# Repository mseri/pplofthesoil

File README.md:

# People of the Soil
**(co-winners of the London Nasa Space Apps Challenge 2013)** 

During the Space Apps Challenge 2013, at the Google Campus in London, we have developed **Project Soil**: an extremely cheap and easy to use system to collect and manage soil data.

We kept in mind that not all the world is as lucky as us and there are plenty of places where internet is slow or completely absent and where there is much less money around. 

**Project Soil** is an open system that includes:

- an extremely cheap (~3£) digital soil testing kit to collect data, and eventually send it
- a light protocol to send the data using web, apps or even SMS and collect it on a centralised database
- an API to disseminate information via SMS or web
- a wonderful and light web application that can run on old and recent phones and gives access to the data with a simple and nice interface.

# Project Soil

We spent the first part of the challeng looking at all our different backgrounds and skills and reformulating the challenge in a series of smaller ones that we feelt we could face. 

As you can see from the image below, **Project Soil** is made by three big interlaced projects, each of them with a particular focus: acquiring data, collecting it and make it available.

## The probe

In this part of the projected we aimed to create a proof-of-concept soil testing kit that could be miniaturised and mass produced. This can then upload recorded soil data, taken over a period of several weeks, to a central database via a phone application or computer interface.

The hardware team realized in an amazingly short time a working prototype of probe to collect soil data. In the first version an Arduino was collecting data from various sensors and sending it to a Rasperry Pi programmed to forward it to our database.

In addition, the aim was to create a PCB schematic and layout to implement this system realistically and cost such a device. CAD models were created to aid development and concept presentation.

The project uses a DS18B20 temperature sensor and a transistor amplified simple moisture sensor.

Moisture is displayed as an estimated percentage volume of water to soil. Completely soaked soil will hold up to around 50% water content and so a measurement of resistance of pure water is taken as the calibration mark for 50% and the probe held in air is taken as the calibration for 0%.

The hardware prototype is a proof of concept, a final device should use a much cheaper MPU such as an ATMEGA48A-MU 4K memory, 8-Bit MPU. This can be sourced (in bulk) for less than 80p per unit.

### The probe and its price breakdown

In fact, from that prototype the hardware team engineered a small and cheap device that you can simply plug in the field and leave alone collecting the data. Afterward it is enough to have a USB connection to collect the data and send it to our servers.

For whom may be interested, the price of the final device can be overestimated as follows:

- ATMEGA48A £0.80   
- Resistor £0.10   
- DS18B20 £0.85   
- CR2032 Coin Cell £0.39   
- Coin cell holder £0.20   
- PCB manufacture £1.00   

**Total £3.34**

## The SMS service

Keeping in mind that not all the world is covered by internet, we used the twilio API to create a service to send the data directly through SMS. This makes it good for use in more developing regions of the world.

Send a text to _01952 787011_ containing a list of readings for the following parameters pH, temperature, moisture, lat/latitude and long/longitude and then will be added to the dataset. The list of key, values can be separated by whitespace or , delimited and the order doesn't matter

```
pH = 7.2, lat=51.9972, long=-0.7421, temp=35
```

You will receive back a message confirming the data your sent and that it had been saved to the database.

## Data collection

While the SMS data goes directly to the database, all the rest of the communication is made by means of [MQTT](http://mqtt.org), a machine-to-machine (M2M)/"Internet of Things" connectivity protocol designed to be extremely lightweight. In this way we can move all the management of the data to our server and consume as less power and bandwith as possible on the clients.

## Web App

Again keeping in mind to consume as less bandwith as possible, we designed and developed an extremely intuitive and nice application, completely based on HTML and CSS, and with nearly no image. In this way people can access the data using any device, not just the last generation of smartphones, consuming nearly no bandwidth!

You can already test our web app going to [Project Soil App](http://www.soil-app.appspot.com/)

## Ideas for the future
The possible implications and improvement for the future are the most variuos. Here there is a small list of what we could and would like to achieve:

- Implementations of more chemical and pH sensors could be made extremely cheaply and in bulk by using thick film printing processes. _This could be an avenue for further development although the technology is still heavily in it's infancy._
- Improve the probe to make it cheaper, stronger and with longer battery life.
- Add wifi/bluetooth/NFC capability to a bigger version of the probe that would not require laptop, smartphones or raspberry pi to send the data.
- Create an easy to use application to collect and send the data from probes that cannot be connected to wifi or bluetooth networks.
- Make the system independent from us and working on a global scale.
- Add some finer controls on the database to avoid fake data.
- Implement a robust and flexible API to make the soil data available to researchers and any other in need.
- Improve the Web App to include data analysis, comparisons and infographics.
- Add support to other languages.
- Go to other planet (see below).

## Project Soil on other Planets
And with our small collaboration with solsola we are ready to fly on the space and collect extra terrestrial soil data!

# More Images and Informations

Look what we did going to the [Git Hub page](https://github.com/mseri/pplofthesoil), looking for our [hashtag #pplofthesoil](http://bit.ly/124FU89) on Twitter, watching our [presentation](http://bit.ly/ZIbJ3x) or reading our ["storified" weekend story](http://bit.ly/17dYVqT)

Additionally you can read:  
- [Our video on Vimeo](http://vimeo.com/65080796)  
- [Soil Testing Kit Challenge](http://spaceappschallenge.org/challenge/soil-testing-kit)
- [People of the Soil -- Project Page](http://spaceappschallenge.org/project/people-of-the-soil/)

Congratulation to all the [winners of the 2013 International Space Apps Challenge](http://open.nasa.gov/blog/2013/05/22/global-award-winners-for-the-2013-international-space-apps-challenge/). 
We didn't win but we've got a Honorable Mention on the Global Impact category!!!!

And thanks to Ben's committment, we have a new, nice and cheap printed Soil PCB:

* * * * * * * 

The Git repository contains:

- The **presentation** of our work: *SOILPres-v3.pdf*
- The full implementation of the **probe** (hardware and software) and the **PCB** schematic to build a cheap and effective probe: *probe* folder
- The interface to the **MQTT** service that translates the data and sends it to the DB: *MQTTinterface* folder
- The **DB and SMS** service (hosted on another Git repo): *text-message-and-database-api* folder
- The **mobile app** to have access to the data: *mobileapp* folder
- A folder **img** with the pictures used in this README files

The project is released under Eclipse Public License 1.0

* * * * * * * * * *    
* * * * * * * * * *    

# Something more technical for us and potential collaborators

## Data structure

Data readings are of the form  

{  
    "id": "182791",  
    "time": "13:56:13 20/04/2013",  
    "lat": "97.03125",  
    "long": "107.2890",  
    "hasAltitude":true,  
    "altitude": "10",  
    "hasPH":true,  
    "pH":"7",  
    "hasMoisture":true,  
    "moisture":"97",  
    "hasTemperature":true,  
    "temperature":"40"  
}  

and must be sent to
- MQTT Broker: m2m.eclipse.org:1833
- Topic: /pots/soil

id, time, lat, long MUST be present and not NULL, otherwise the data is sent directly to /dev/null

It can be done as simple and boring as using <http://mqtt.io/>    
Or you can let your hardware prepare the data and send it using (more or less) any programming language: <http://mqtt.org/software>

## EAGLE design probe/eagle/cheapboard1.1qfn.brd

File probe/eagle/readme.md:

# Arduino Code for PeopleOfTheSoil

It runs on an AVR with an arduino bootloader.

This project is being created in association with the google/NASA space apps challenge. 

#Price Breakdown
ATMEGA48A	 	£0.80 
Resistor	 	£0.10 
DS18B20	 		£0.85 
CR2032 Coin Cell	£0.39 
Coin cell holder	£0.20 
PCB manufacture	 	£1.00 
	 	Total	£3.34 

#Roles
This part of the projected aimed to create a proof-of-concept soil testing kit that
could be miniaturised and mass produced. This can then upload recorded soil data, 
taken over a period of several weeks, to a central database via a phone application
or computer interface.

In addition, the aim was to create a PCB schematic and layout to implement this system
realistically and cost such a device.

CAD models were created to aid development and concept presentation.

#Scope
The views and conclusions contained in the software and documentation are those
of the authors and should not be interpreted as representing official policies, 
either expressed or implied, of the FreeBSD Project.

Project has used the OneWire library to communicate with a DS18B20 temperature 
sensor and a transistor amplified simple moisture sensor.

Moisture is displayed as an estimated percentage volume of water to soil. 
Completely soaked soil will hold up to around 50% water content and so a measurement 
of resistance of pure water is taken as the calibration mark for 50% and the probe 
held in air is taken as the calibration for 0%.

The hardware prototype is a proof of concept, a final device should use a much cheaper
MPU such as an ATMEGA48A-MU 4K memory, 8-Bit MPU. This can be sourced (in bulk) for 
less than 80p per unit.

##Further Work
Implementations of more chemical and pH sensors could be made extremely cheaply and in
bulk by using thick film printing processes. This could be an avenue for further 
development although the technology is still heavily in it's infancy.

## Links
* [Homepage](http://www.benoxley.com/) www.benoxley.com

<p xmlns:dct="http://purl.org/dc/terms/" xmlns:vcard="http://www.w3.org/2001/vcard-rdf/3.0#">
  
  <br />
  To the extent possible under law,
  <a rel="dct:publisher"
     href="www.benoxley.co.uk">
    <span property="dct:title">Ben Oxley</span></a>
  has waived all copyright and related or neighboring rights to
  <span property="dct:title">People of the Soil</span>.
This work is published from:
<span property="vcard:Country" datatype="dct:ISO3166"
      content="GB" about="www.benoxley.co.uk">
  United Kingdom</span>.
</p>

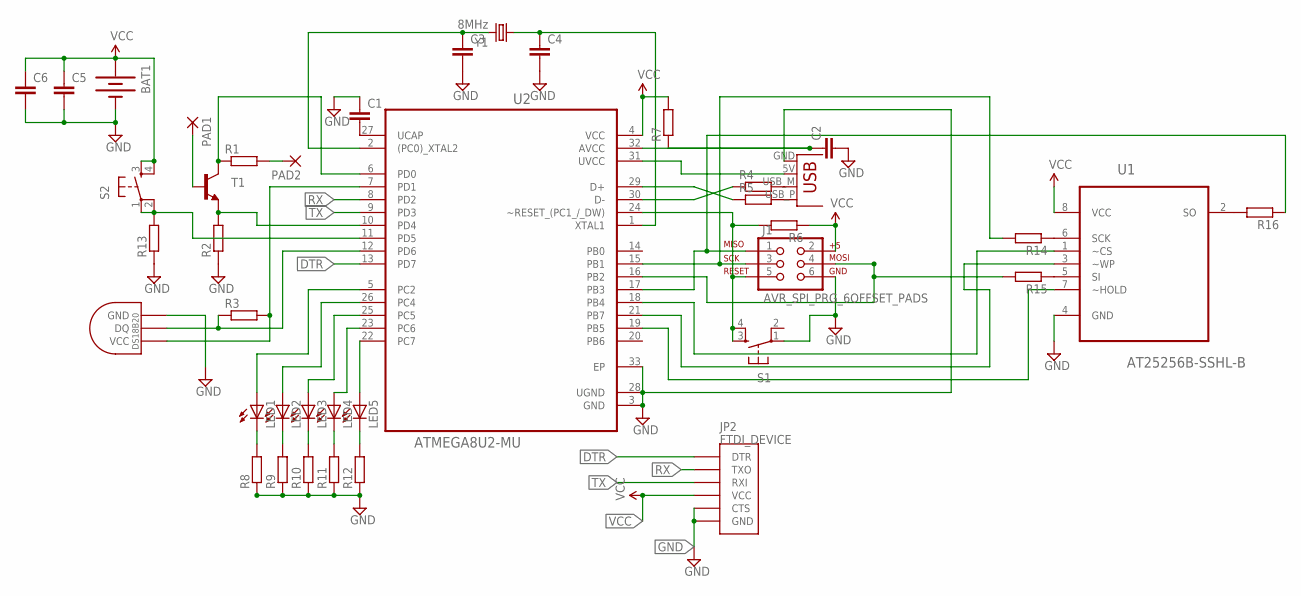
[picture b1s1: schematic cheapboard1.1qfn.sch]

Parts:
BAT1: BATTERY245PTH; BATTCON_245MM_PTH
C1, C2, C3, C4, C5, C6: CAP0805; 0805
J1: AVR_SPI_PRG_6OFFSET_PADS; 2X3_OFFSET
JP1: USBPCB; USB-A-PCB
JP2: FTDI_DEVICE; FTDI_DEVICE_SIDE
LED1, LED2, LED3, LED4, LED5: LEDCHIPLED_0805; CHIPLED_0805
PAD1, PAD2: SMD5; SMD2,54-5,08
R1, R2, R3, R4, R5, R6, R7, R8, R9, R10, R11, R12, R13, R14, R15, R16: R-EU_M0805; M0805
S1, S2: TAC_SWITCHSMD; TACTILE_SWITCH_SMD
T1: TRANSISTOR_NPNSOT23-3; SOT23-3
U1: AT25256B-SSHL-B; SOIC127P600X175-8N
U2: ATMEGA8U2-MU; QFN50P500X500X100-33N
U$1: DS1820SOIC; DS18B20_SOIC
Y1: 8MHz; CRYSTAL-SMD-5X3

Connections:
DTR: JP2.P$1 (DTR), U2.13 (PD7)
GND: BAT1.2 (-), C1.1, C2.2, C3.2, C4.2, C5.2, C6.2, J1.6, JP1.GND, JP2.P$5 (CTS), JP2.P$6 (GND), R2.1, R8.1, R9.1, R10.1, R11.1, R12.1, R13.1, S1.1, U1.4 (GND), U2.3 (GND), U2.28 (UGND), U2.33 (EP), U$1.GND
unnamed: R1.1, T1.3 (C), U2.6 (PD0)
unnamed: J1.4, R15.2, U2.16 (PB2)
unnamed: R2.2, T1.2 (E), U2.10 (PD4)
unnamed: J1.5, R6.2, S1.3, S1.4, U2.24 (~RESET_(PC1_/_DW))
unnamed: J1.3, R14.2, U2.15 (PB1)
unnamed: R3.1, U2.12 (PD6), U$1.DQ
unnamed: J1.1, R16.1, U2.17 (PB3)
unnamed: JP1.5V (VBUS), U2.31 (UVCC)
unnamed: C2.1, R7.1, U2.32 (AVCC)
unnamed: R4.1, U2.30 (D-)
unnamed: R5.1, U2.29 (D+)
unnamed: JP1.USB_M (D-), R4.2
unnamed: JP1.USB_P (D+), R5.2
unnamed: R3.2, U2.7 (PD1), U$1.VCC
unnamed: R14.1, U1.6 (SCK)
unnamed: C1.2, U2.27 (UCAP)
unnamed: C4.1, U2.1 (XTAL1), Y1.1
unnamed: C3.1, U2.2 ((PC0)_XTAL2), Y1.3 (2)
unnamed: LED1.A, U2.5 (PC2)
unnamed: LED2.A, U2.26 (PC4)
unnamed: LED3.A, U2.25 (PC5)
unnamed: LED4.A, U2.23 (PC6)
unnamed: LED5.A, U2.22 (PC7)
unnamed: LED1.C, R8.2
unnamed: LED2.C, R9.2
unnamed: LED3.C, R10.2
unnamed: LED4.C, R11.2
unnamed: LED5.C, R12.2
unnamed: R15.1, U1.5 (SI)
unnamed: R13.2, S2.1, S2.2, U2.11 (PD5)
unnamed: R16.2, U1.2 (SO)
unnamed: U1.1 (~CS), U2.18 (PB4)
unnamed: U1.3 (~WP), U2.21 (PB7)
unnamed: U1.7 (~HOLD), U2.19 (PB5)
PAD1: PAD1.1, T1.1 (B)
PAD2: PAD2.1, R1.2
RX: JP2.P$2 (TXO), U2.8 (PD2)
TX: JP2.P$3 (RXI), U2.9 (PD3)
VCC: BAT1.3 (+), C5.1, C6.1, J1.2, JP2.P$4 (VCC), R6.1, R7.2, S2.3, S2.4, U1.8 (VCC), U2.4 (VCC)

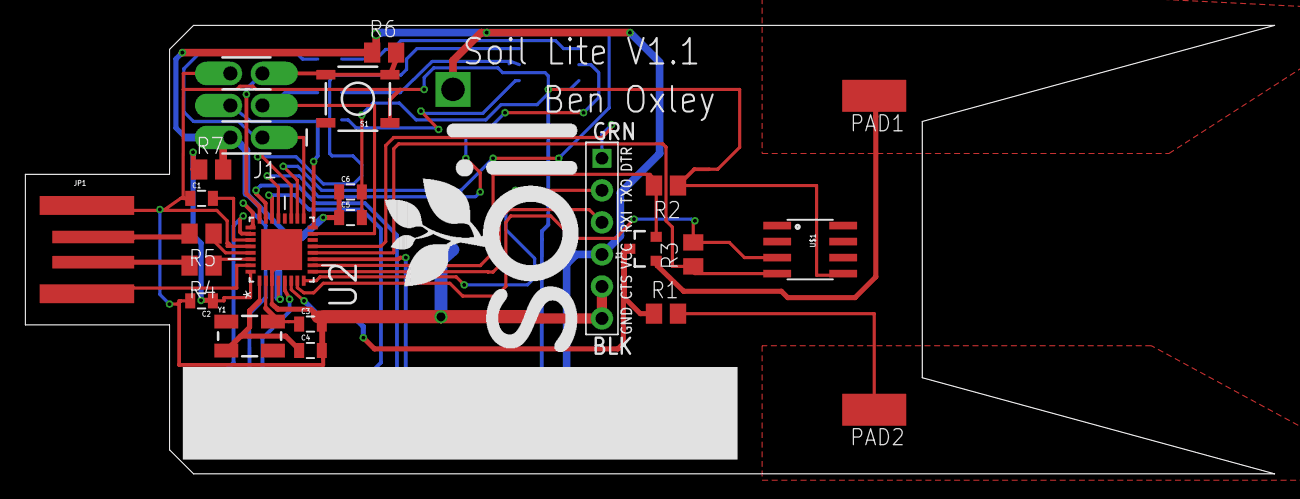
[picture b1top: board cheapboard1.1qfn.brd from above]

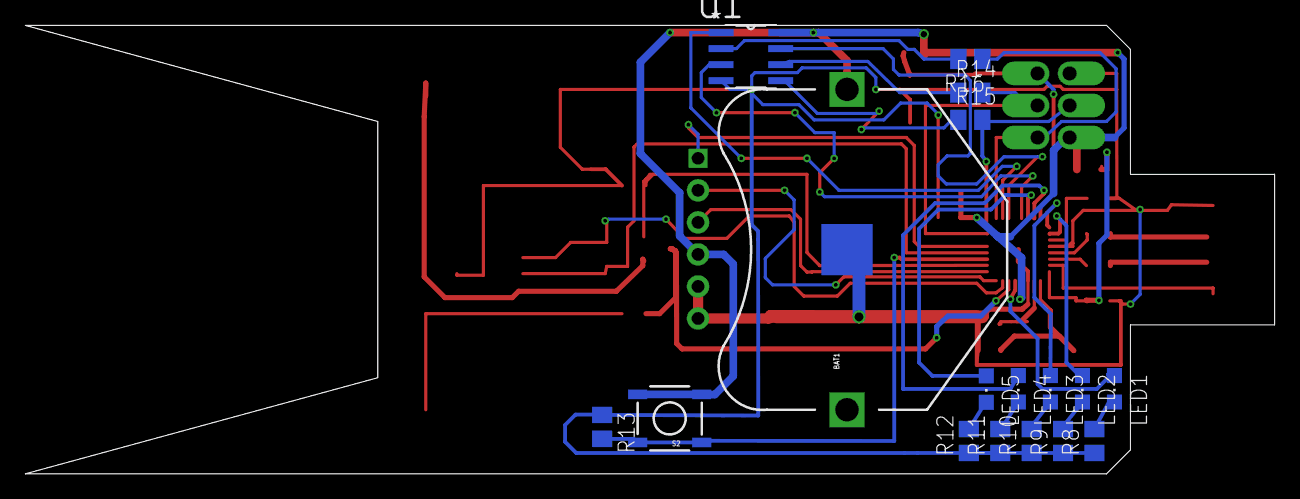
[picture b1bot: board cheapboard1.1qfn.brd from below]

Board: 2 copper layers, 99.1 x 35.6 mm, 40 parts (17 on the bottom side), 41 nets.

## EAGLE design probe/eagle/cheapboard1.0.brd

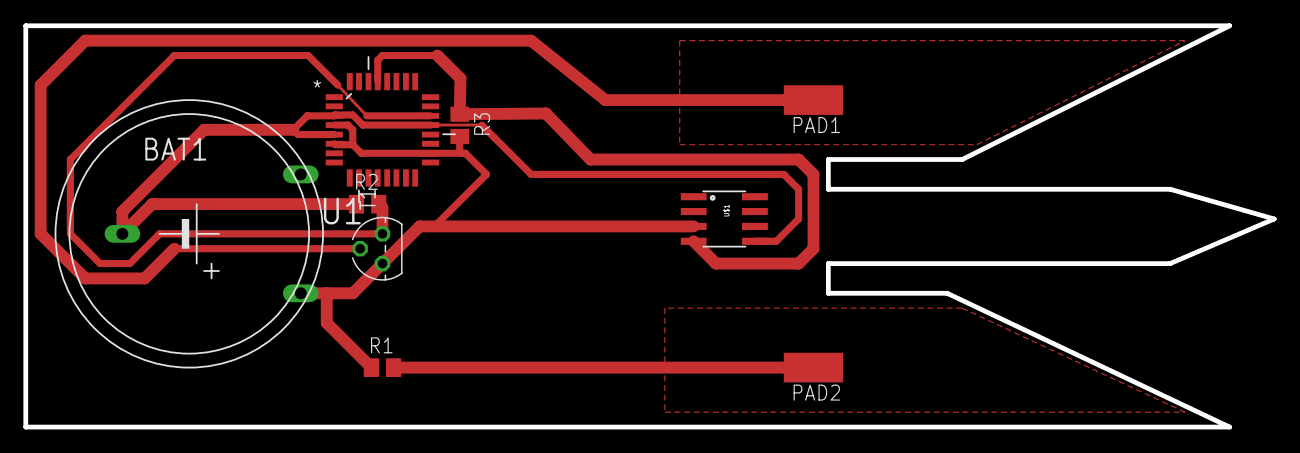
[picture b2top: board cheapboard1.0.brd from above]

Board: 2 copper layers, 106.7 x 34.3 mm, 9 parts (0 on the bottom side), 6 nets.

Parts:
BAT1: BATTERY
PAD1, PAD2: SMD2,54-5,08
R1, R2, R3: M0805
T1: BC547; TO92
U1: ATMEGA48A-AU; QFP80P900X900X120-32N
U$1: DS1820SOIC; DS18B20_SOIC

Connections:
GND: BAT1.-, R2.1, U1.3, U1.5, U1.21, U$1.GND
unnamed: BAT1.+, R1.1, R3.2, T1.3, U1.4, U1.6, U1.18, U$1.VCC
unnamed: R2.2, T1.1, U1.22
unnamed: R3.1, U1.29, U$1.DQ
PAD1: PAD1.1, T1.2
PAD2: PAD2.1, R1.2

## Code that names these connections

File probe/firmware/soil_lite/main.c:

/*
Project Soil V1.1 Firmware V0.1

This program is made for Project Soil proceeding from the 
Google Space Apps Challenge. Please find more information at:
http://spaceappschallenge.org/project/people-of-the-soil/
or
https://github.com/mseri/pplofthesoil

Ben Oxley 2013

LEDs are on Pins 22(PC7),23(PC6),25(PC5),26(PC4) and 5(PC2)
*/

#include <avr/io.h>
#include <stdio.h>
#include <util/delay.h>
#include <avr/eeprom.h>
#include <avr/interrupt.h>
#include <string.h>
#include <stdbool.h>
#include <stdlib.h>
#include <avr/wdt.h>

#define output_low(port,pin) port &= ~(1<<pin)
#define output_high(port,pin) port |= (1<<pin)
#define set_input(portdir,pin) portdir &= ~(1<<pin)
#define set_output(portdir,pin) portdir |= (1<<pin)

void delay_ms(uint8_t ms) {
	uint16_t delay_count = F_CPU / 17500;
	volatile uint16_t i;

	while (ms != 0) {
		for (i=0; i != delay_count; i++);
			ms--;
	}
}

int main(void)
{
	DDRC |= 0xFF;
	while(true){
	  output_high(PORTC, PC7);
      _delay_ms(500);
      output_low(PORTC, PC7);
      _delay_ms(500);
	}
	return 0;
}

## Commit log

2013-04-20 README updated
2013-04-20 Data structure and other minimal infos on the README
2013-04-20 Data structure correction on the readme First preliminary version of the MMQT listener
2013-04-20 Ruby MQTT listener to interface with the DB service
2013-04-20 Minor corrections
2013-04-20 comments and logs improved
2013-04-20 Added arduino code
2013-04-20 corrections on the README
2013-04-20 Added arduino readme
2013-04-20 New folder structure
2013-04-20 Log files are more structured, added definition of servers and logfile at the beginning of the file
2013-04-20 Debug messages commented
2013-04-20 Minor changes
2013-04-20 Listener rewritten as method listenToMQTTForSoilData(brokerAddress,dataManagerAddress,logFile,debugLevel)
2013-04-20 correction of comments… nothing important
2013-04-20 Added additional error controls Improved configurable debug verbosity
2013-04-20 Now the JSON is stripped (remove spaces before and after : and remove \n and \r). In this way we can parse the message even if it is not exactly in standard ruby JSON
2013-04-20 Updated readme for people that want to join
2013-04-20 Adding RaspberryPi files.
2013-04-20 Updated readme for arduino
2013-04-20 More modular structure of the listener + first sketch of a daemon version of the same sw. BE CAREFUL: the daemon version is not working
2013-04-21 Rewritten listener: more modular and now with a background daemon version and a CLI version. Comments improved. Logging improved.
2013-04-21 Solved small bug that prevented the running if the log folder was not present
2013-04-21 Added BEER-WARE rev. 42 license to all the files
2013-04-21 Added UUID for arduino device, updated license file to CC0
2013-04-21 Added Random Number library for UUID
2013-04-21 Null fields are translated to nil and not deleted.
2013-04-21 README corrections
2013-04-21 Added control on NULL values
2013-04-21 Bug fixes
2013-04-21 Improved communication
2013-04-21 better log
2013-04-21 added the text message and database project
2013-04-21 Added electronics layout
2013-04-21 Soil mobile app initial commit
2013-04-21 updating things
2013-04-21 added correct submodule
2013-04-21 Added pcb files
2013-04-21 Added pictures :D
2013-04-21 Added PCB readme
2013-04-21 settings updated
2013-04-22 Updated Readme. Added Presentation. Small reshaping of the folder structure
2013-04-22 Unknown changes
2013-04-22 Better quality presentation
2013-04-22 Improved README
2013-04-22 renamed folder in MQTTinterface
2013-04-22 Added README in MQTT, corrections in global README, corrections in MQTT license description
2013-04-22 Added Low-Quality presentation
2013-04-22 As before
2013-04-22 ibid
2013-04-23 Compatibility with 1.9.3.
    Added small 'fake data generator' for tests (generate 15 different messages in more or less the same amount of time)
2013-04-23 fake messages were not 100% correct, now they are ok
2013-04-24 Log messages improved
2013-04-24 Added gitignore
2013-04-24 Added many many new PCB files
2013-04-24 Added many many files
2013-04-24 Finished adding many files
2013-04-24 Corrected bug that prevent Daemonized version to skip bad data
2013-04-24 Resolved Bug related to logging on new systems
2013-04-25 Improved README with pictures and more detailed descriptions
2013-04-25 Corrected image sizes
2013-04-25 Small correction
2013-04-25 small corrections
2013-04-26 Removed description and use of SMS ansewer system as requested by Growers Nation
2013-04-26 Image replaced
2013-04-26 More on the Hardware
2013-04-26 Improved SMS data input description
2013-04-26 corrections on my .gitignore
2013-04-26 changed Soil with Project Soil to be coherent with the video
2013-04-29 Added link to the video
2013-04-29 Adding STL files and images for probe case prototype.
2013-04-30 Added readme to probe case section.
2013-05-06 Added final design for v1.1 manufacture
2013-05-22 We've got an Honorable Mention! :)
2013-06-02 Create gh-pages branch via GitHub
2013-06-08 Added some research
2013-06-08 Added start of testing files for firmware

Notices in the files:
probe/eagle/readme.md:
href="http://creativecommons.org/publicdomain/zero/1.0/">
parts and their libraries:
SparkFun-Connectors: Licensing: CC v3.0 Share-Alike You are welcome to use this library for commercial purposes.
